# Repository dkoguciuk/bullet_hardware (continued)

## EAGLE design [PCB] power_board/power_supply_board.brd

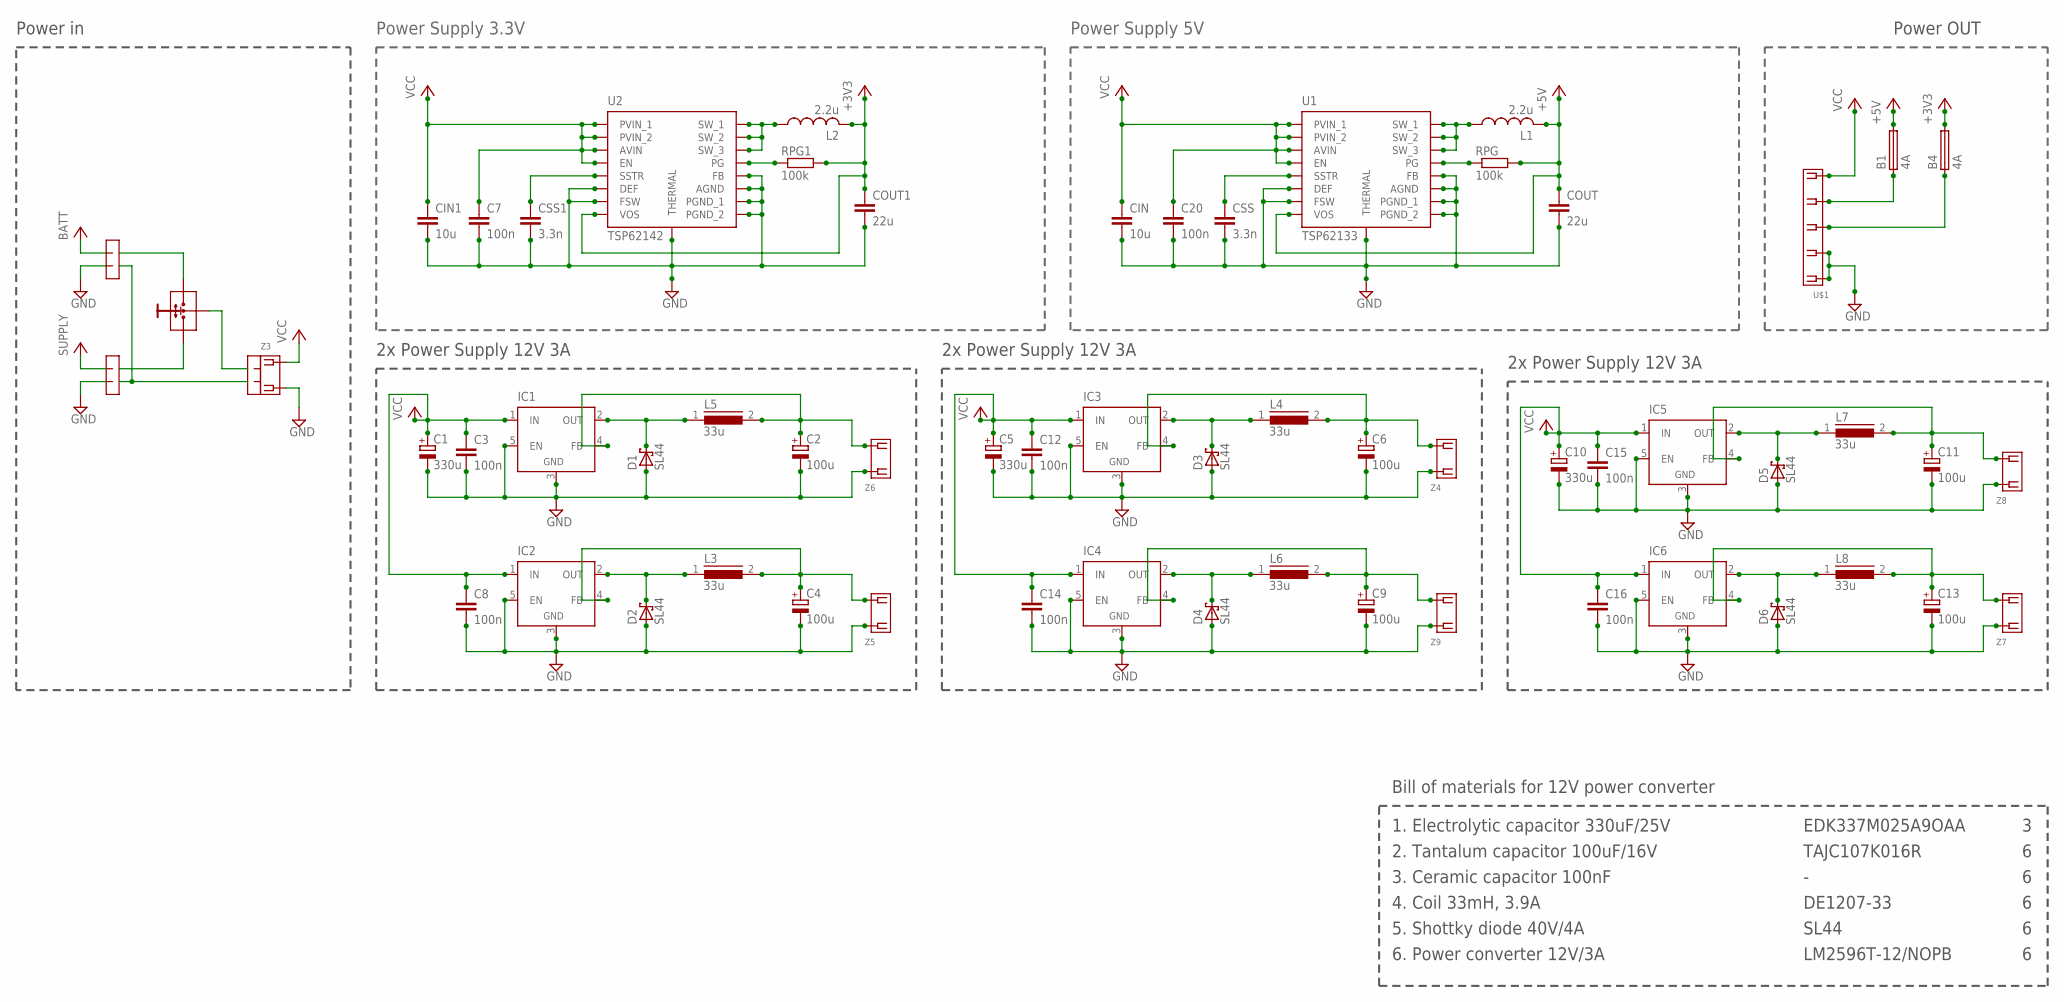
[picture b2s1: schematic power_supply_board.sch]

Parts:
B1, B4: 4A; 1206
C1, C5, C10: 330u; 150CLZ-1010
C2, C4, C6, C9, C11, C13: 100u; SMC_C
C3, C7, C8, C12, C14, C15, C16, C20: 100n; C0805
CIN, CIN1: 10u; C0805
COUT, COUT1: 22u; C0805
CSS, CSS1: 3.3n; C0805
D1, D2, D3, D4, D5, D6: SL44; SMC
IC1, IC2, IC3, IC4, IC5, IC6: LM2596TV; TO220-51
L1, L2: 2.2u; POWER-CHOKE_WE-TPC
L3, L4, L5, L6, L7, L8: 33u; DR127
RPG, RPG1: 100k; R0805
U1: TSP62133
U2: TSP62142
U$1: MOLEX-5268-05
Z3: 2EDGRC-5
Z4, Z5, Z6, Z7, Z8, Z9: MOLEX-5268-02

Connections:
12V3A_1: C2.+, IC1.4 (FB), L5.2, Z6.P$2 (2)
12V3A_2: C4.+, IC2.4 (FB), L3.2, Z5.P$2 (2)
12V3A_3: C6.+, IC3.4 (FB), L4.2, Z4.P$2 (2)
12V3A_4: C9.+, IC4.4 (FB), L6.2, Z9.P$2 (2)
12V3A_5: C11.+, IC5.4 (FB), L7.2, Z8.P$2 (2)
12V3A_6: C13.+, IC6.4 (FB), L8.2, Z7.P$2 (2)
+3V3: B4.2, COUT1.1, L2.2, RPG1.2, U2.VOS
+5V: B1.2, COUT.1, L1.2, RPG.2, U1.VOS
GND: C1.-, C2.-, C3.2, C4.-, C5.-, C6.-, C7.2, C8.2, C9.-, C10.-, C11.-, C12.2, C13.-, C14.2, C15.2, C16.2, C20.2, CIN.2, CIN1.2, COUT.2, COUT1.2, CSS.2, CSS1.2, D1.A, D2.A, D3.A, D4.A, D5.A, D6.A, IC1.3 (GND), IC1.5 (EN), IC2.3 (GND), IC2.5 (EN), IC3.3 (GND), IC3.5 (EN), IC4.3 (GND), IC4.5 (EN), IC5.3 (GND), IC5.5 (EN), IC6.3 (GND), IC6.5 (EN), U1.AGND, U1.DEF, U1.FB, U1.FSW, U1.PGND_1, U1.PGND_2, U1.THERMAL, U2.AGND, U2.DEF, U2.FB, U2.FSW, U2.PGND_1, U2.PGND_2, U2.THERMAL, U$1.P$1 (1), U$1.P$2 (2), Z3.P$2 (2), Z4.P$1 (1), Z5.P$1 (1), Z6.P$1 (1), Z7.P$1 (1), Z8.P$1 (1), Z9.P$1 (1)
unnamed: CSS.1, U1.SSTR
unnamed: L2.1, U2.SW_1, U2.SW_2, U2.SW_3
unnamed: RPG1.1, U2.PG
unnamed: CSS1.1, U2.SSTR
unnamed: D2.C, IC2.2 (OUT), L3.1
unnamed: D3.C, IC3.2 (OUT), L4.1
unnamed: L1.1, U1.SW_1, U1.SW_2, U1.SW_3
unnamed: D4.C, IC4.2 (OUT), L6.1
unnamed: RPG.1, U1.PG
unnamed: D5.C, IC5.2 (OUT), L7.1
unnamed: D6.C, IC6.2 (OUT), L8.1
unnamed: D1.C, IC1.2 (OUT), L5.1
unnamed: B1.1, U$1.P$4 (4)
unnamed: B4.1, U$1.P$3 (3)
VCC: C1.+, C3.1, C5.+, C7.1, C8.1, C10.+, C12.1, C14.1, C15.1, C16.1, C20.1, CIN.1, CIN1.1, IC1.1 (IN), IC2.1 (IN), IC3.1 (IN), IC4.1 (IN), IC5.1 (IN), IC6.1 (IN), U1.AVIN, U1.EN, U1.PVIN_1, U1.PVIN_2, U2.AVIN, U2.EN, U2.PVIN_1, U2.PVIN_2, U$1.P$5 (5), Z3.P$1 (1)

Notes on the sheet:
Power Supply 3.3V
Power in
Power OUT
2x Power Supply 12V 3A
Power Supply 5V
Bill of materials for 12V power converter
1. Electrolytic capacitor 330uF/25V
EDK337M025A9OAA
2. Tantalum capacitor 100uF/16V
TAJC107K016R
3. Ceramic capacitor 100nF
4. Coil 33mH, 3.9A
DE1207-33
5. Shottky diode 40V/4A
SL44
6. Power converter 12V/3A
LM2596T-12/NOPB

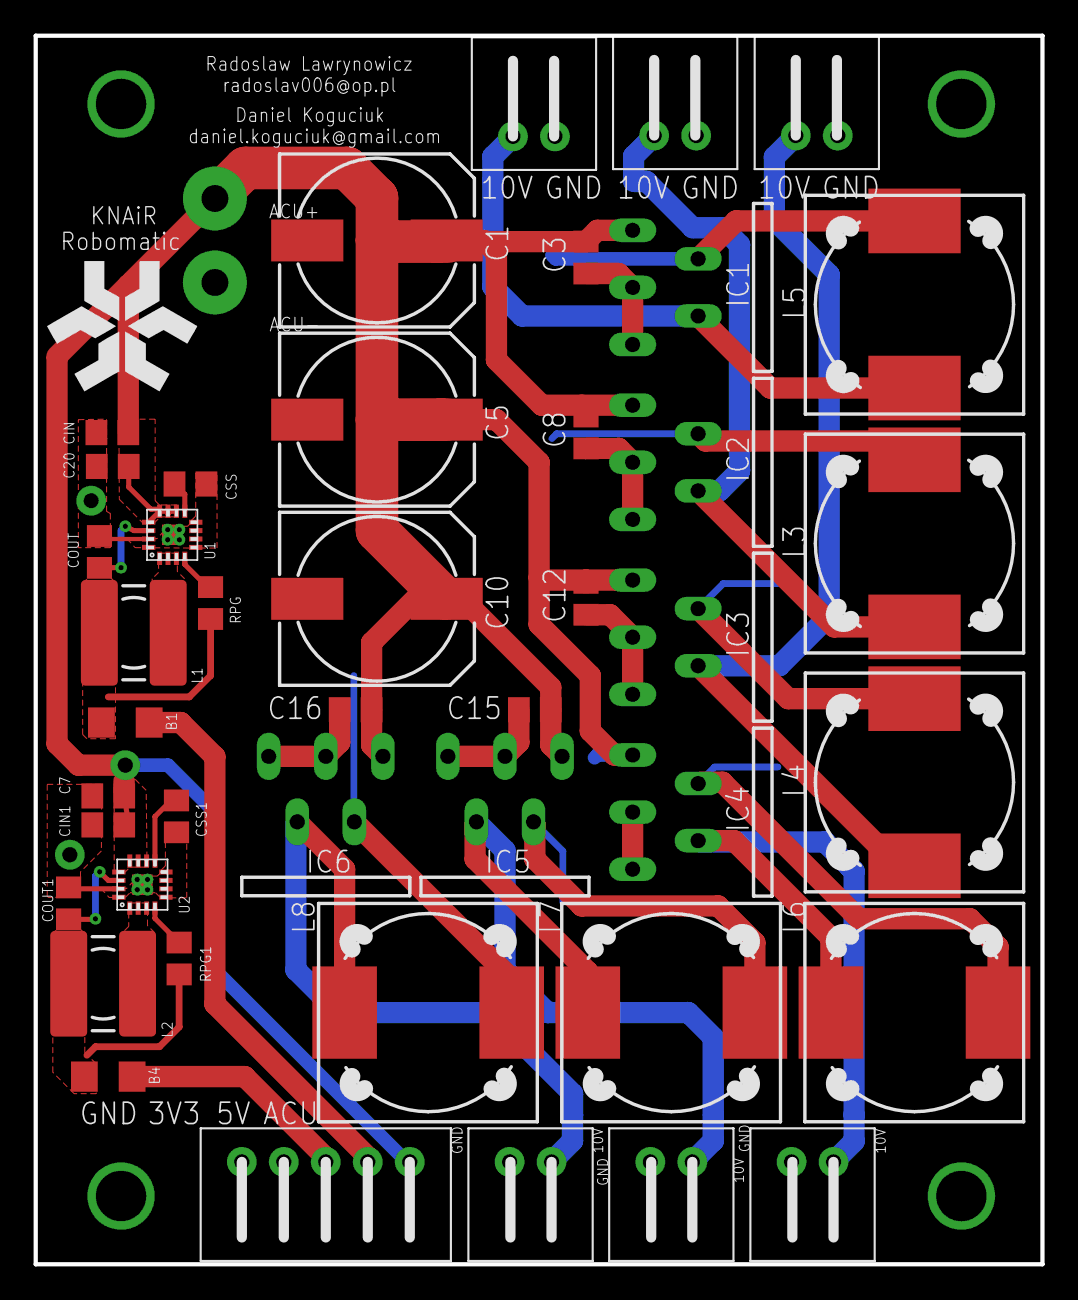
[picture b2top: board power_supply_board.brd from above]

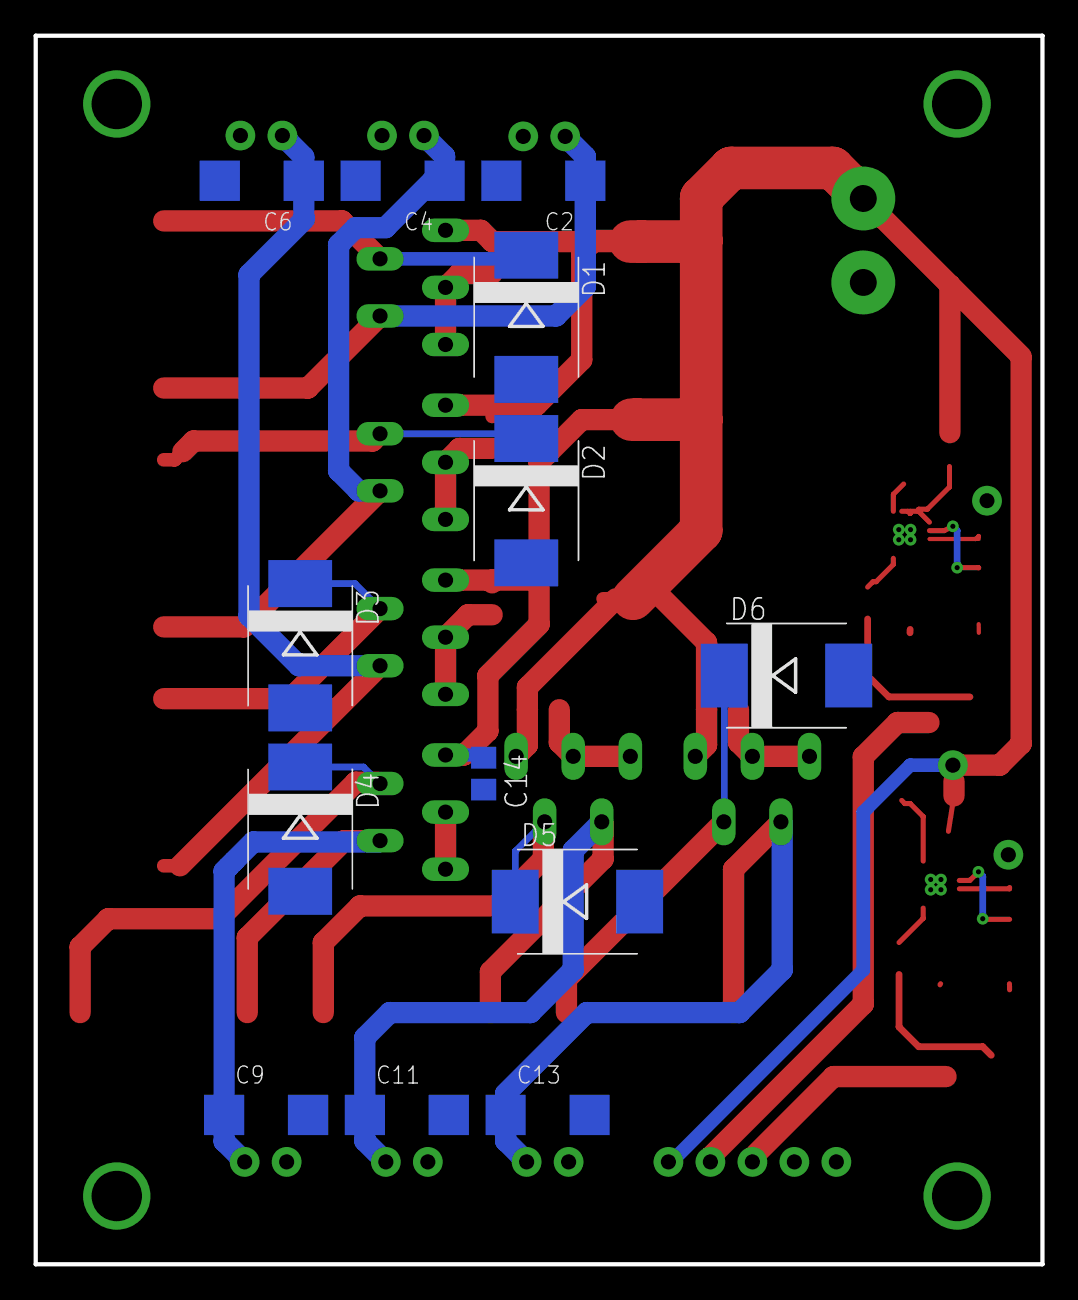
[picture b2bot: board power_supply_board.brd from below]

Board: 2 copper layers, 59.9 x 73.2 mm, 57 parts (13 on the bottom side), 24 nets.

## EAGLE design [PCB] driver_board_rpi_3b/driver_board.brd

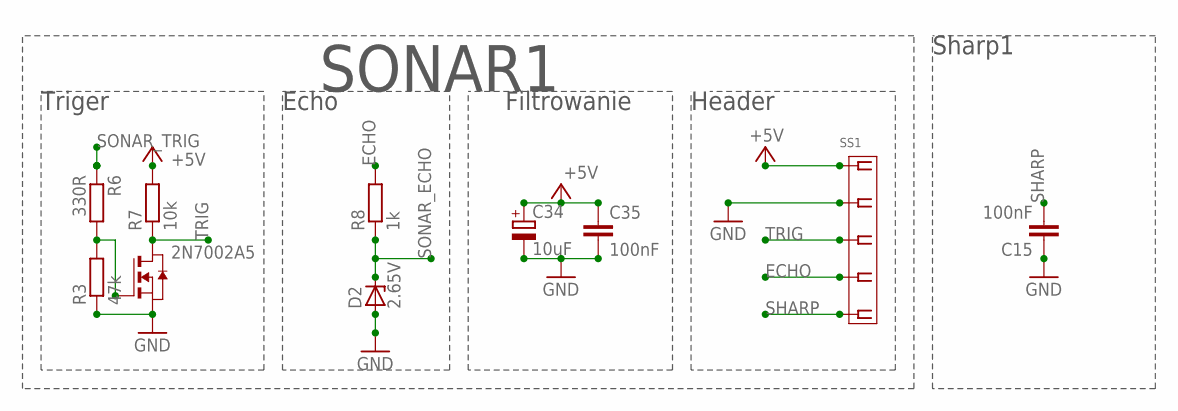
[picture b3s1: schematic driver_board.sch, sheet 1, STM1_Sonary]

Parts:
2N7002A5: NMOSSOT23; SOT-23
C15, C35: 100nF; C0805
C34: 10uF; SMC_A
D2: 2.65V; SOT23
R3: 47k; R0805
R6: 330R; R0805
R7: 10k; R0805
R8: 1k; R0805
SS1: MOLEX-5268-05

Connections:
+5V: C34.+, C35.1, R7.2, SS1.P$1 (1); also elsewhere on the board
ECHO: R8.2, SS1.P$4 (4)
GND: 2N7002A5.2 (S), C15.1, C34.-, C35.2, D2.1 (A), R3.1, SS1.P$2 (2); also elsewhere on the board
unnamed: 2N7002A5.3 (G), R3.2, R6.2
SHARP: C15.2, SS1.P$5 (5); also elsewhere on the board
SONAR_ECHO: D2.3 (C), R8.1; also elsewhere on the board
SONAR_TRIG: R6.1; also elsewhere on the board
TRIG: 2N7002A5.1 (D), R7.1, SS1.P$3 (3)

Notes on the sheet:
Triger
Filtrowanie
Echo
SONAR1
Header
Sharp1

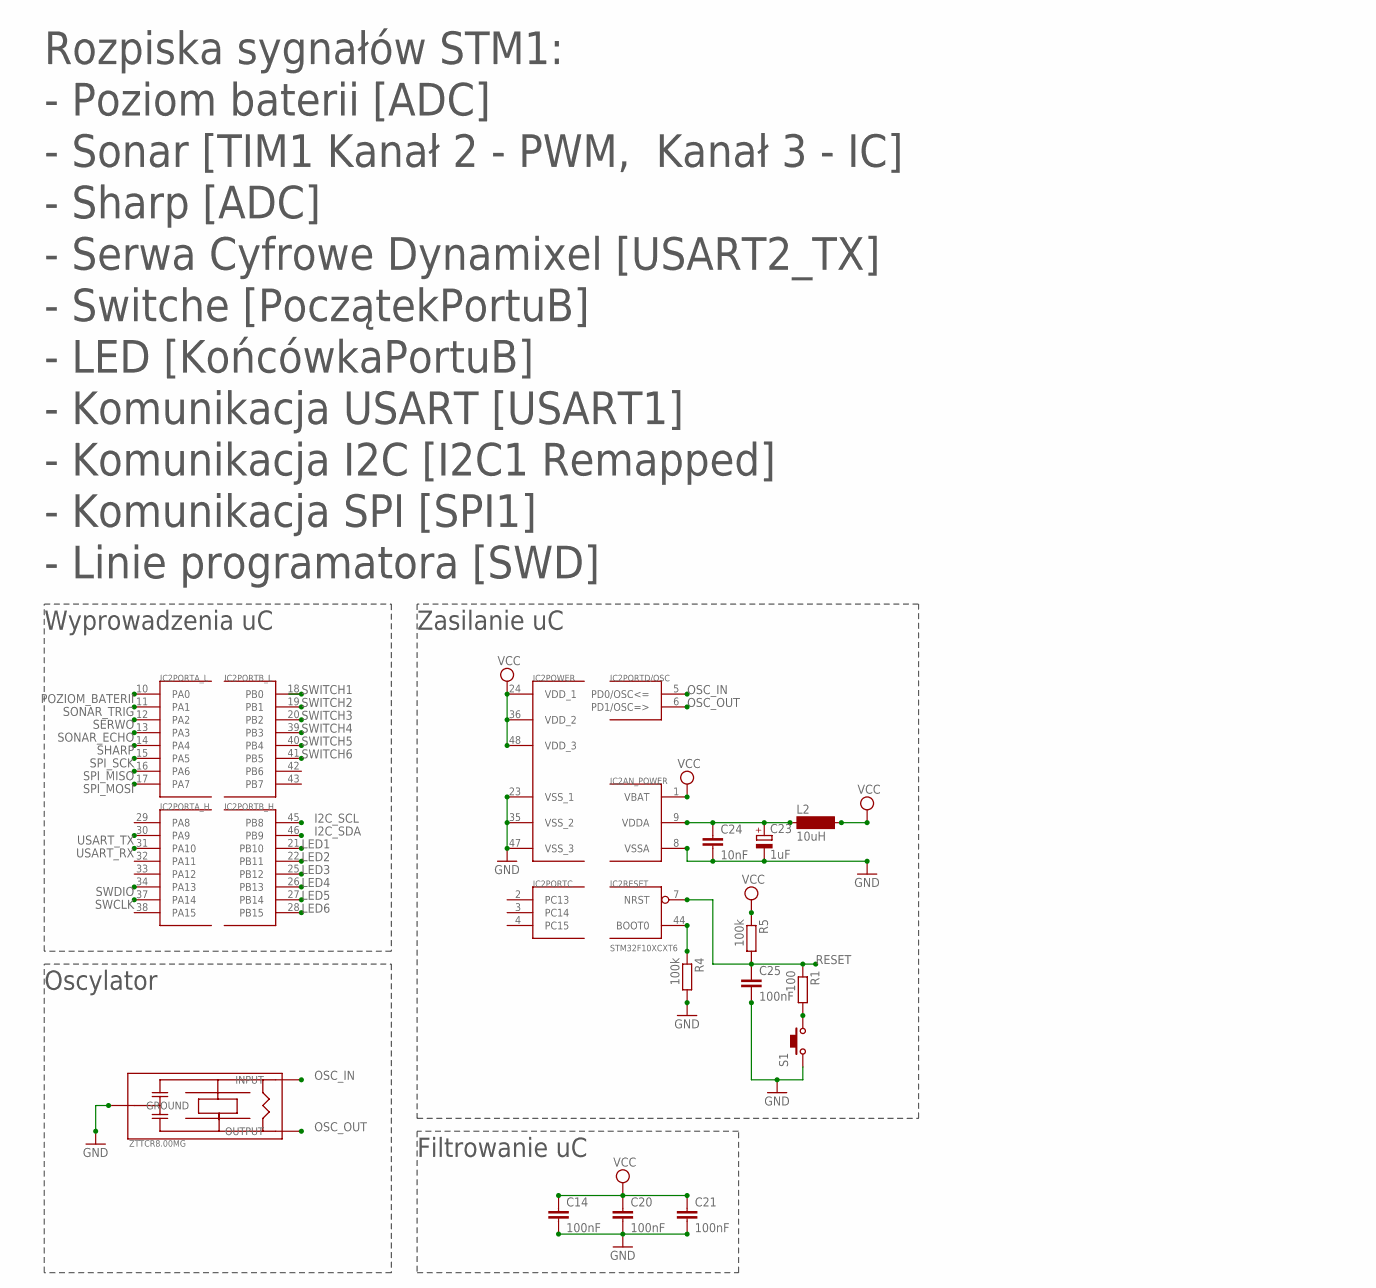
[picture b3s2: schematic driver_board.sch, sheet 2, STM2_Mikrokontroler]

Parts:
C14, C20, C21, C25: 100nF; C0805
C23: 1uF; SMC_A
C24: 10nF; C0805
IC2: STM32F10XCXT6; TQFP48
L2: 10uH; SM-1206
R1: 100; R0805
R4, R5: 100k; R0805
S1: TACT-6XX-SMD
U$8: ZTTCR8.00MG

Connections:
GND: C14.2, C20.2, C21.2, C23.-, C24.2, C25.2, IC2.8 (VSSA), IC2.23 (VSS_1), IC2.35 (VSS_2), IC2.47 (VSS_3), R4.2, S1.P$1 (1), U$8.GROUND; also elsewhere on the board
I2C_SCL: IC2.45 (PB8); also elsewhere on the board
I2C_SDA: IC2.46 (PB9); also elsewhere on the board
LED1: IC2.21 (PB10); also elsewhere on the board
LED2: IC2.22 (PB11); also elsewhere on the board
LED3: IC2.25 (PB12); also elsewhere on the board
LED4: IC2.26 (PB13); also elsewhere on the board
LED5: IC2.27 (PB14); also elsewhere on the board
LED6: IC2.28 (PB15); also elsewhere on the board
unnamed: R1.2, S1.P$3 (4)
unnamed: C23.+, C24.1, IC2.9 (VDDA), L2.1
unnamed: IC2.44 (BOOT0), R4.1
OSC_IN: IC2.5 (PD0/OSC<=), U$8.INPUT
OSC_OUT: IC2.6 (PD1/OSC=>), U$8.OUTPUT
POZIOM_BATERII: IC2.10 (PA0); also elsewhere on the board
RESET: C25.1, IC2.7 (NRST), R1.1, R5.2
SERWO: IC2.12 (PA2); also elsewhere on the board
SHARP: IC2.14 (PA4); also elsewhere on the board
SONAR_ECHO: IC2.13 (PA3); also elsewhere on the board
SONAR_TRIG: IC2.11 (PA1); also elsewhere on the board
SPI_MISO: IC2.16 (PA6); also elsewhere on the board
SPI_MOSI: IC2.17 (PA7); also elsewhere on the board
SPI_SCK: IC2.15 (PA5); also elsewhere on the board
SWCLK: IC2.37 (PA14); also elsewhere on the board
SWDIO: IC2.34 (PA13); also elsewhere on the board
SWITCH1: IC2.18 (PB0); also elsewhere on the board
SWITCH2: IC2.19 (PB1); also elsewhere on the board
SWITCH3: IC2.20 (PB2); also elsewhere on the board
SWITCH4: IC2.39 (PB3); also elsewhere on the board
SWITCH5: IC2.40 (PB4); also elsewhere on the board
SWITCH6: IC2.41 (PB5); also elsewhere on the board
USART_RX: IC2.31 (PA10); also elsewhere on the board
USART_TX: IC2.30 (PA9); also elsewhere on the board
VCC: C14.1, C20.1, C21.1, IC2.1 (VBAT), IC2.24 (VDD_1), IC2.36 (VDD_2), IC2.48 (VDD_3), L2.2, R5.1; also elsewhere on the board

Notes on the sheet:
Wyprowadzenia uC
Zasilanie uC
Oscylator
Filtrowanie uC
Rozpiska sygnałów STM1:
- Komunikacja USART [USART1]
- Komunikacja SPI [SPI1]
- Serwa Cyfrowe Dynamixel [USART2_TX]
- Komunikacja I2C [I2C1 Remapped]
- Switche [PoczątekPortuB]
- LED [KońcówkaPortuB]
- Linie programatora [SWD]
- Poziom baterii [ADC]
- Sonar [TIM1 Kanał 2 - PWM, Kanał 3 - IC]
- Sharp [ADC]

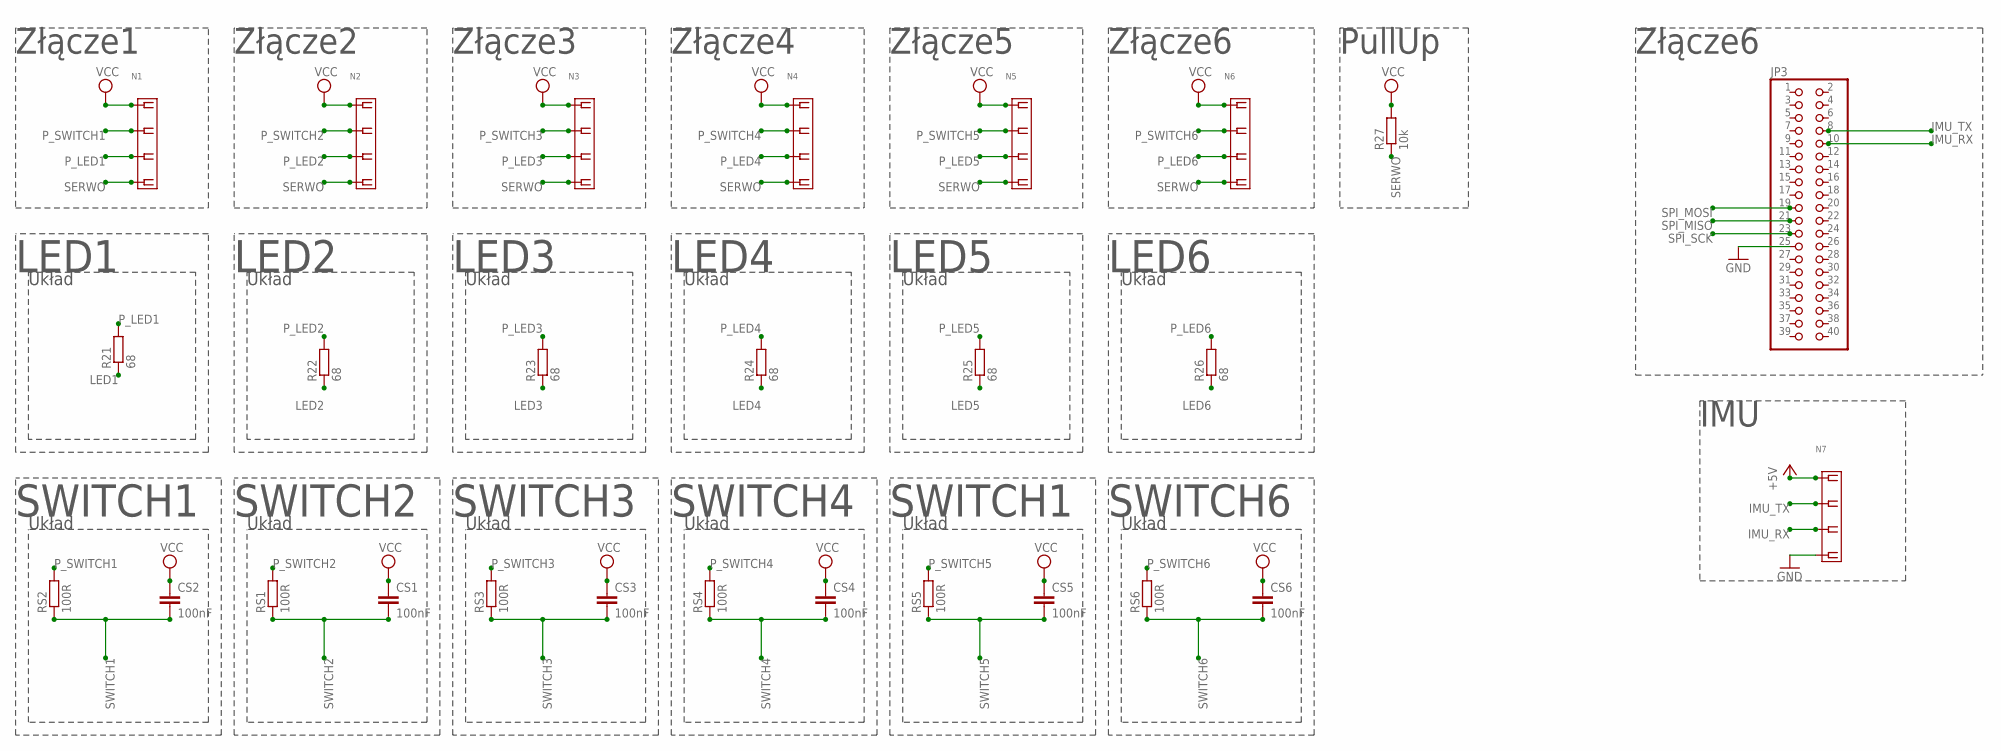
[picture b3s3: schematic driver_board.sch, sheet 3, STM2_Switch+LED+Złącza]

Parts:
CS1, CS2, CS3, CS4, CS5, CS6: 100nF; C0805
JP3: PINHD-2X20; 2X20
N1, N2, N3, N4, N5, N6, N7: MOLEX-5268-04
R21, R22, R23, R24, R25, R26: 68; R0805
R27: 10k; R0805
RS1, RS2, RS3, RS4, RS5, RS6: 100R; R0805

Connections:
+5V: N7.P$1 (1); also elsewhere on the board
GND: JP3.25, N7.P$4 (4); also elsewhere on the board
IMU_RX: JP3.10, N7.P$3 (3)
IMU_TX: JP3.8, N7.P$2 (2)
LED1: R21.1; also elsewhere on the board
LED2: R22.1; also elsewhere on the board
LED3: R23.1; also elsewhere on the board
LED4: R24.1; also elsewhere on the board
LED5: R25.1; also elsewhere on the board
LED6: R26.1; also elsewhere on the board
P_LED1: N1.P$3 (3), R21.2
P_LED2: N2.P$3 (3), R22.2
P_LED3: N3.P$3 (3), R23.2
P_LED4: N4.P$3 (3), R24.2
P_LED5: N5.P$3 (3), R25.2
P_LED6: N6.P$3 (3), R26.2
P_SWITCH1: N1.P$2 (2), RS2.2
P_SWITCH2: N2.P$2 (2), RS1.2
P_SWITCH3: N3.P$2 (2), RS3.2
P_SWITCH4: N4.P$2 (2), RS4.2
P_SWITCH5: N5.P$2 (2), RS5.2
P_SWITCH6: N6.P$2 (2), RS6.2
SERWO: N1.P$4 (4), N2.P$4 (4), N3.P$4 (4), N4.P$4 (4), N5.P$4 (4), N6.P$4 (4), R27.1; also elsewhere on the board
SPI_MISO: JP3.21; also elsewhere on the board
SPI_MOSI: JP3.19; also elsewhere on the board
SPI_SCK: JP3.23; also elsewhere on the board
SWITCH1: CS2.2, RS2.1; also elsewhere on the board
SWITCH2: CS1.2, RS1.1; also elsewhere on the board
SWITCH3: CS3.2, RS3.1; also elsewhere on the board
SWITCH4: CS4.2, RS4.1; also elsewhere on the board
SWITCH5: CS5.2, RS5.1; also elsewhere on the board
SWITCH6: CS6.2, RS6.1; also elsewhere on the board
VCC: CS1.1, CS2.1, CS3.1, CS4.1, CS5.1, CS6.1, N1.P$1 (1), N2.P$1 (1), N3.P$1 (1), N4.P$1 (1), N5.P$1 (1), N6.P$1 (1), R27.2; also elsewhere on the board

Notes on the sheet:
Układ
SWITCH1
LED1
LED2
LED3
LED4
LED5
LED6
Złącze1
SWITCH2
SWITCH3
SWITCH4
SWITCH6
PullUp
Złącze2
Złącze3
Złącze4
Złącze5
Złącze6
IMU

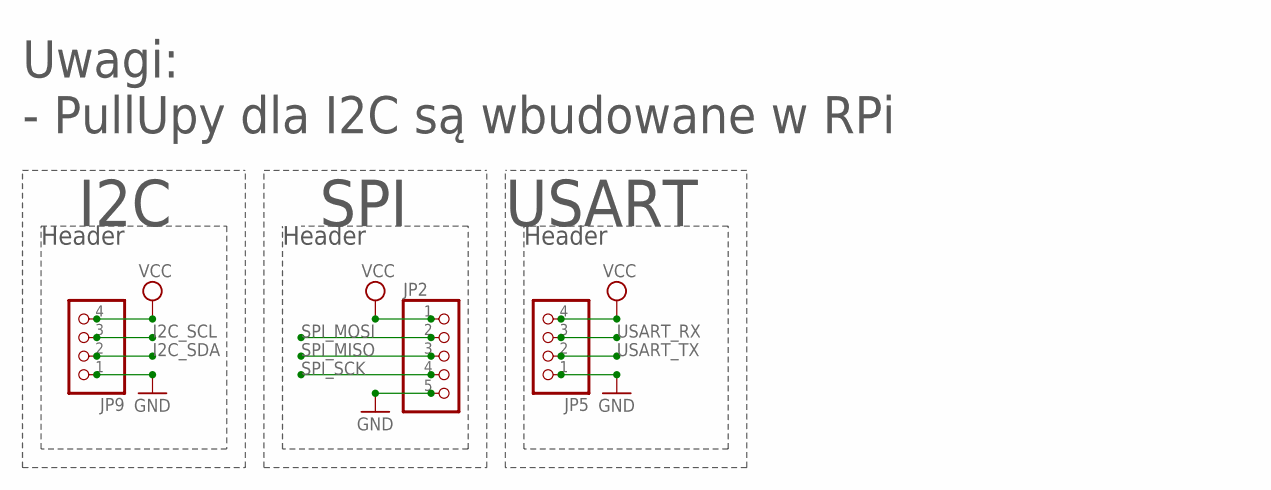
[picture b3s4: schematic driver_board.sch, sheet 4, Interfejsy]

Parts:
JP2: PINHD-1X5; 1X05
JP5, JP9: PINHD-1X4; 1X04

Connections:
GND: JP2.5, JP5.1, JP9.1; also elsewhere on the board
I2C_SCL: JP9.3; also elsewhere on the board
I2C_SDA: JP9.2; also elsewhere on the board
SPI_MISO: JP2.3; also elsewhere on the board
SPI_MOSI: JP2.2; also elsewhere on the board
SPI_SCK: JP2.4; also elsewhere on the board
USART_RX: JP5.3; also elsewhere on the board
USART_TX: JP5.2; also elsewhere on the board
VCC: JP2.1, JP5.4, JP9.4; also elsewhere on the board

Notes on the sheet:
Header
I2C
SPI
USART
Uwagi:
- PullUpy dla I2C są wbudowane w RPi

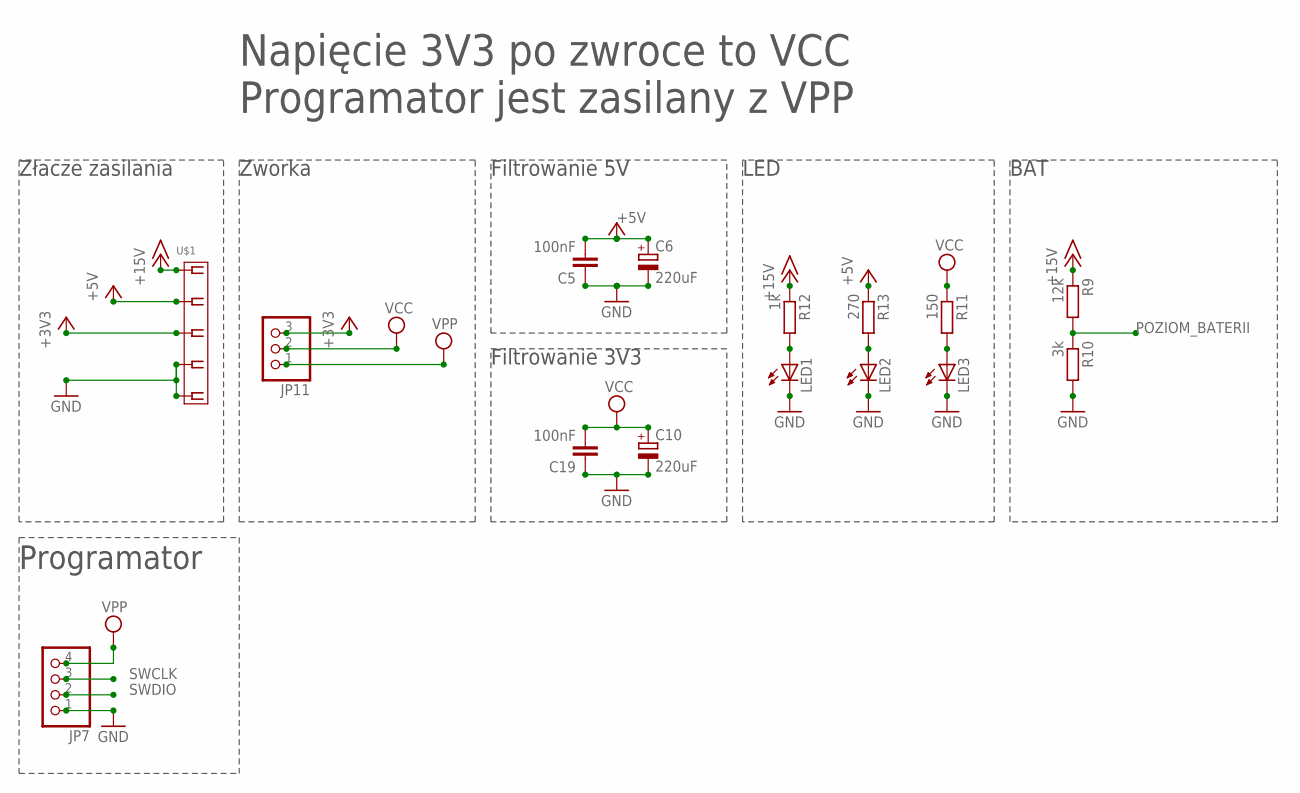
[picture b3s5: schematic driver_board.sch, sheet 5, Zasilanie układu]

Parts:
C5, C19: 100nF; C0805
C6, C10: 220uF; SMC_A
JP7: PINHD-1X4; 1X04
JP11: PINHD-1X3; 1X03
LED1, LED2, LED3: LEDCHIPLED_0805; CHIPLED_0805
R9: 12k; R0805
R10: 3k; R0805
R11: 150; R0805
R12: 1k; R0805
R13: 270; R0805
U$1: MOLEX-5268-05

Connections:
+3V3: JP11.3, U$1.P$3 (3)
+5V: C5.2, C6.+, R13.1, U$1.P$2 (2); also elsewhere on the board
+15V: R9.1, R12.1, U$1.P$1 (1)
GND: C5.1, C6.-, C10.-, C19.1, JP7.1, LED1.C, LED2.C, LED3.C, R10.2, U$1.P$4 (4), U$1.P$5 (5); also elsewhere on the board
unnamed: LED2.A, R13.2
unnamed: LED3.A, R11.2
unnamed: LED1.A, R12.2
POZIOM_BATERII: R9.2, R10.1; also elsewhere on the board
SWCLK: JP7.3; also elsewhere on the board
SWDIO: JP7.2; also elsewhere on the board
VCC: C10.+, C19.2, JP11.2, R11.1; also elsewhere on the board
VPP: JP7.4, JP11.1

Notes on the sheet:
Zworka
Programator jest zasilany z VPP
Napięcie 3V3 po zwroce to VCC
Filtrowanie 5V
Filtrowanie 3V3
Programator
Złacze zasilania
LED
BAT

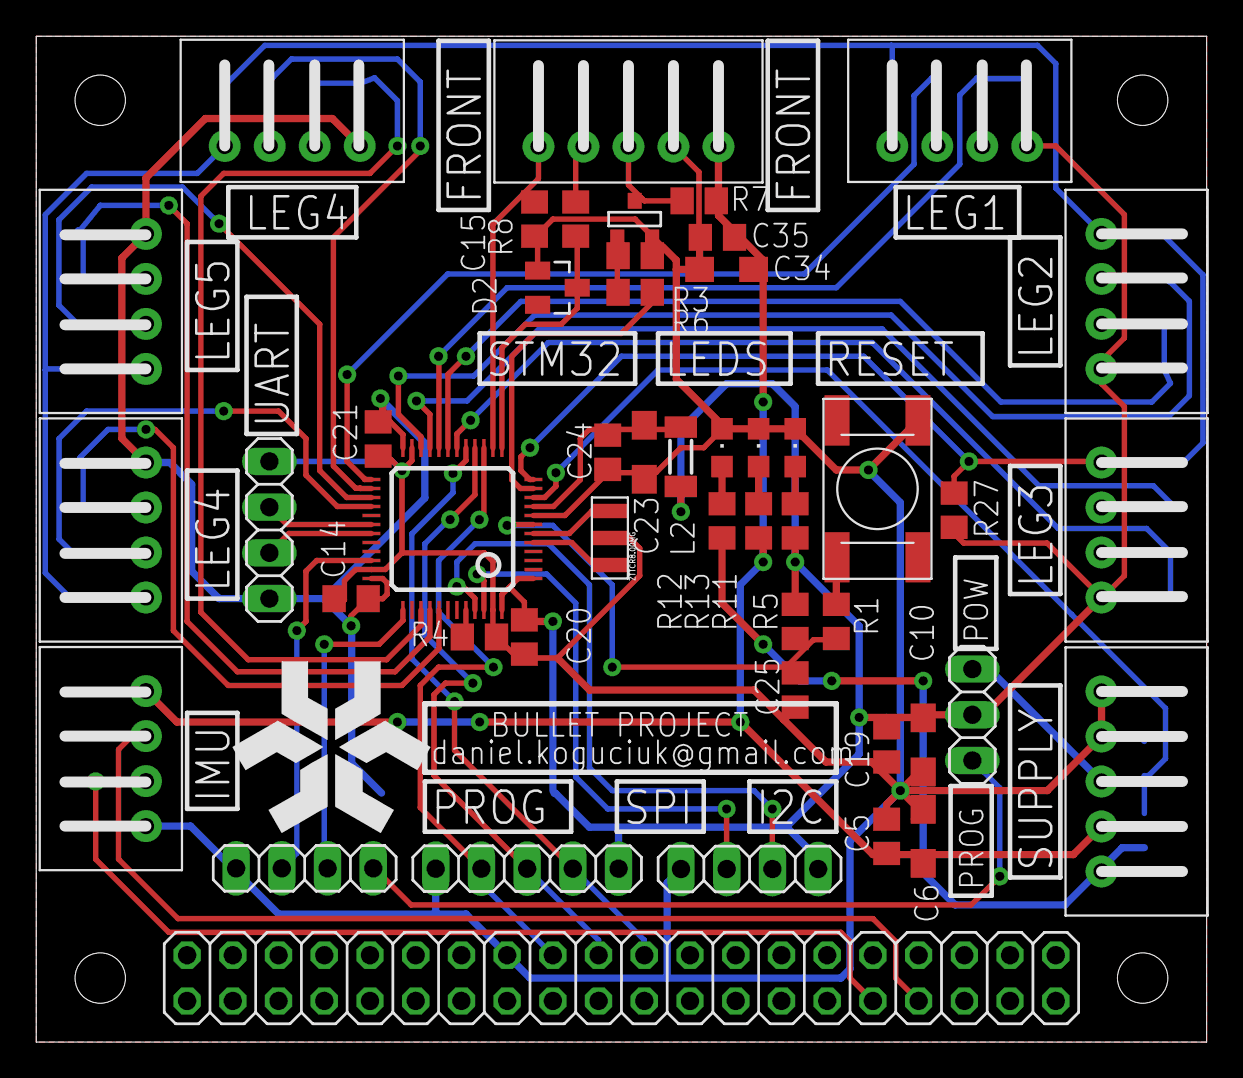
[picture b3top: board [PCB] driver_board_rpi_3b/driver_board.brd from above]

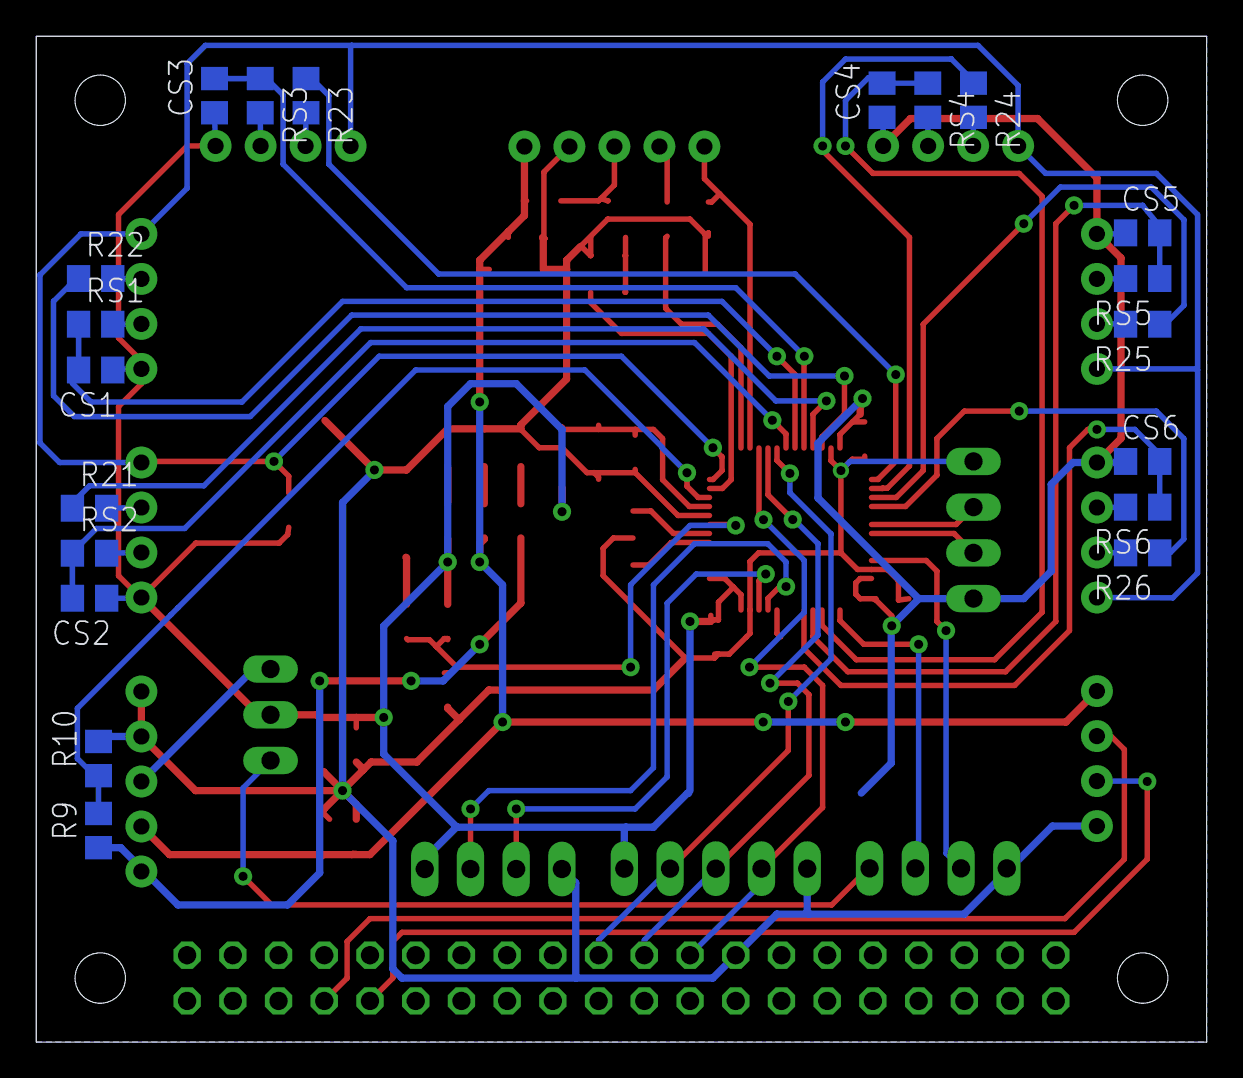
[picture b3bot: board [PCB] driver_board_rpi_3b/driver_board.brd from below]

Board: 2 copper layers, 65.0 x 55.9 mm, 68 parts (20 on the bottom side), 58 nets.

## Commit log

2017-07-19 Pushing repo to github.
2017-07-21 Added small render image.
